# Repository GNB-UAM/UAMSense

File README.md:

# UAMSense electronic nose design
Artificial nose design with multimodal sensing capabilities.

___These are experimental designs. Use at your own risk.___

Please see Bibtex and other citation options at the bottom of the page.

UAMSense 4
==========

UAMSense 3
==========

UAMSense 2
==========

UAMSense 1
==========

UART-BME680
===========

I2C-Sensors
===========

License
=======
For source code: GPLv3 <https://www.gnu.org/licenses/gpl-3.0.en.html>

For hardware: Attribution-ShareAlike 4.0 International <https://creativecommons.org/licenses/by-sa/4.0/>

© Carlos Garcia-Saura 2023

Cite as
=======

Scientific papers:
- Garcia-Saura C., Rodriguez-Lujan I., Serrano E., Rodríguez F.B. and Varona P., At-home monitorization using artificial noses
and multimodal sensors: a noninvasive approach to human routine certification. IBJ Plus 2022 1(s5) e00017. DOI: 10.24217/2531-
0151.22v1s5.00017. https://doi.org/10.24217/2531-0151.22V1S5.00017

PhD Thesis:
```bibtex
@phdthesis{garciasaura2023,
  title={Exploration and characterization of environments under uncertainty using multimodal sensors},
  author={Garcia-Saura, Carlos},
  year={2023},
  school={Escuela Politecnica Superior, Universidad Autonoma de Madrid}
}
```

UAMSense project (this repository):
```bibtex
@misc{uamsense2023,
  author = {Garcia-Saura, Carlos},
  title = {UAMSense electronic nose design},
  publisher = {GitHub},
  year = {2023},
  doi = {10.5281/ZENODO.10442698},
  url = {https://doi.org/10.5281/zenodo.10442698}
}
```

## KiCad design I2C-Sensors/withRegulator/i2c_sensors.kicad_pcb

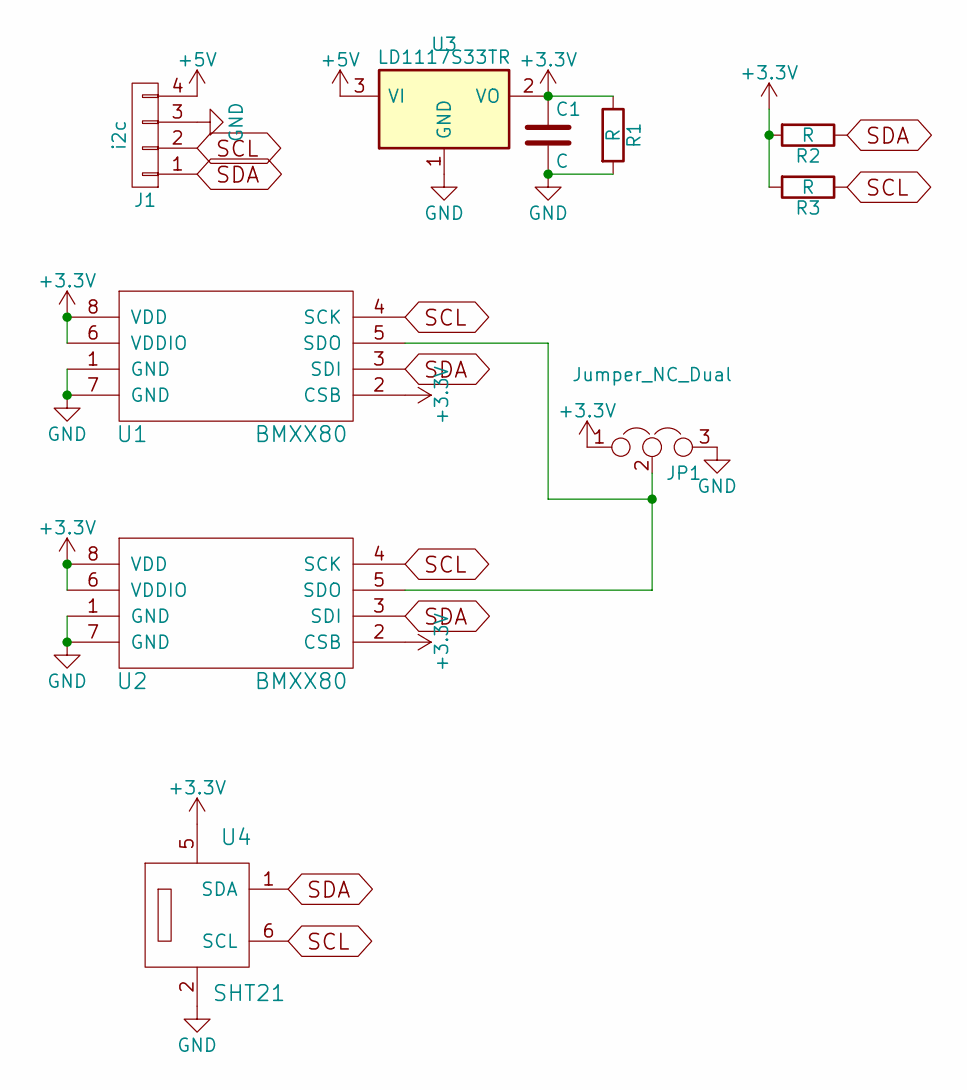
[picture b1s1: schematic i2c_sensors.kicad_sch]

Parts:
C1: C; C_0805
J1: i2c; Pin_Header_Straight_1x04_Pitch2.54mm
JP1: Jumper_NC_Dual; Pin_Header_Straight_1x03_Pitch2.54mm
R1, R2, R3: R; R_0805
U1, U2: BMXX80; BME280
U3: LD1117S33TR; SOT-223
U4: SHT21; DFN-6-1EP_3x3mm_Pitch0.95mm

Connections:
+3V3: C1.1, JP1.1, R1.1, R2.2, R3.2, U1.2 (CSB), U1.6 (VDDIO), U1.8 (VDD), U2.2 (CSB), U2.6 (VDDIO), U2.8 (VDD), U3.2 (VO), U4.5
+5V: J1.4, U3.3 (VI)
GND: C1.2, J1.3, JP1.3, R1.2, U1.1 (GND), U1.7 (GND), U2.1 (GND), U2.7 (GND), U3.1 (GND), U4.2
unnamed: JP1.2, U1.5 (SDO), U2.5 (SDO)
SCL: J1.2, R3.1, U1.4 (SCK), U2.4 (SCK), U4.6 (SCL)
SDA: J1.1, R2.1, U1.3 (SDI), U2.3 (SDI), U4.1 (SDA)

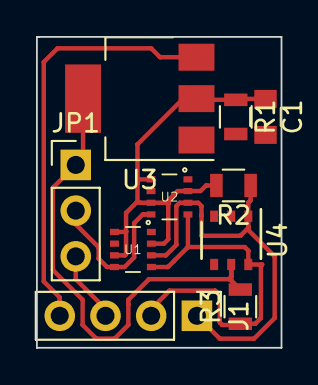
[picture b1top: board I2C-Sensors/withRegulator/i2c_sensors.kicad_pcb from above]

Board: 2 copper layers, 13.6 x 17.3 mm, 10 parts (0 on the bottom side), 6 nets.

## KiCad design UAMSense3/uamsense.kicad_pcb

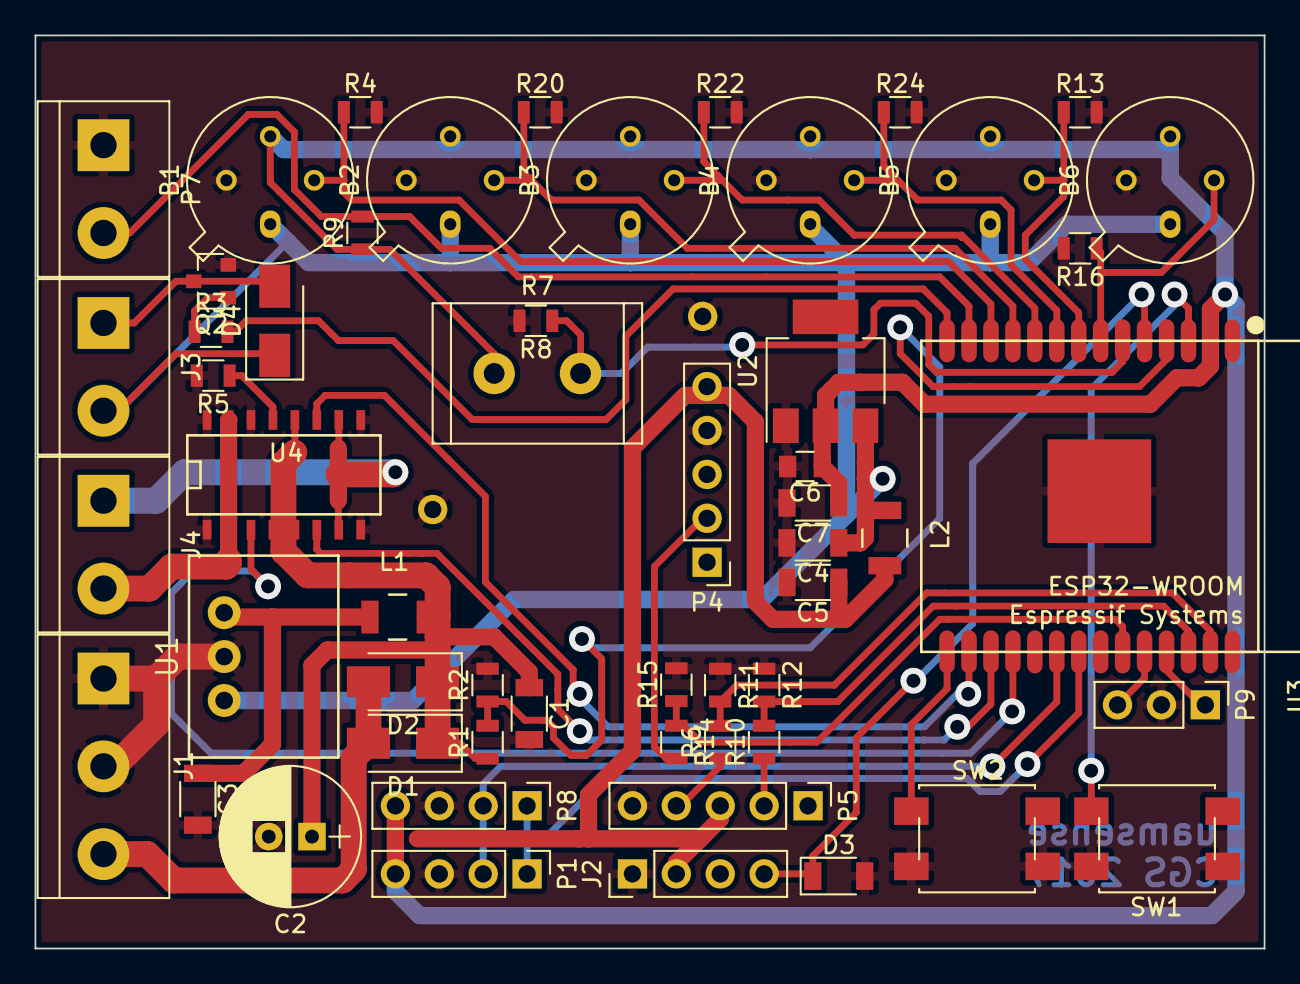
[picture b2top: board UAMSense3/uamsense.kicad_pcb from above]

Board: 2 copper layers, 71.1 x 52.8 mm, 57 parts (0 on the bottom side), 38 nets.

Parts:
B1, B2, B3, B4, B5, B6: TGS2600; TO-5-4
C1, C3, C4, C5, C7: 10u; C_1206
C2: 270u; CP_Radial_D8.0mm_P2.50mm
C6: 100n; C_0805
D1, D2, D4: D_Schottky; D_SMA
D3: 3.3V; D_1206
J1: power; bornier3
J2, J2#2, J2#3: loudness; Pin_Header_Straight_1x04_Pitch2.54mm
J3: fan; bornier2
J4: peltier; bornier2
L1, L2: 33u; Neosid_Inductor_SM-NE30_SMD1210
P1: I2C; Socket_Strip_Straight_1x04_Pitch2.54mm
P4: CDM7160; Socket_Strip_Straight_1x05_Pitch2.54mm
P5: DSM501A; Socket_Strip_Straight_1x05_Pitch2.54mm
P7: door; bornier2
P8: I2C; Pin_Header_Straight_1x04_Pitch2.54mm
P9: SERIAL; Pin_Header_Straight_1x03_Pitch2.54mm
Q2: BSS138; SOT-23
R1: R1batt; R_0805
R2: R2batt; R_0805
R3: Rfan; R_0805
R4, R13, R16, R20, R22, R24: Rtgs; R_0805
R5: RsenseH; R_0805
R6, R10: R1dust; R_0805
R7: Photores; R_Radial_Power_L12.0mm_W8.0mm_P5.00mm
R8: Rlight; R_0805
R9: Rdoor; R_0805
R11, R12: R2dust; R_0805
R14: R1co2; R_0805
R15: R2co2; R_0805
SW1: RESET; smd_button
SW2: BOOT; smd_button
U1: R-78E5.0-0.5
U2: LD1117S33TR; SOT-223
U3: ESP32-WROOM
U4: VNH7070AS; SO-16-N

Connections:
+3V3: B1.3, B2.3, B3.3, B4.3, B5.3, B6.3, C6.1, C7.1, P1.4, P8.4, R7.1, R9.1, U2.2, U3.2
+5V: C5.1, J2#3.2, L2.2, P4.5, P5.3
+5VD: B1.1, B2.1, B3.1, B4.1, B5.1, B6.1, C4.1, D4.1, J3.2, L2.1, U1.3, U2.3
+BATT: C1.1, C2.1, D1.1, D2.1, L1.2, R1.1, U4.4, U4.5, U4.12
GND: B1.4, B2.4, B3.4, B4.4, B5.4, B6.4, C1.2, C2.2, C3.2, C4.2, C5.2, C6.2, C7.2, D3.2, J1.1, J1.2, J2.1, J2#2.1, J2#3.1, P1.3, P4.4, P5.5, P7.1, P8.3, P9.2, Q2.2, R2.2, R4.2, R5.2, R8.2, R11.1, R12.1, R13.2, R15.2, R16.2, R20.2, R22.2, R24.2, SW1.1, SW2.2, U1.2, U2.1, U3.1, U3.38, U3.39, U4.1, U4.8, U4.9, U4.14, U4.16
HinA: U3.28, U4.3
HinB: U3.27, U4.6
Hpwm: U3.26, U4.11
unnamed: C3.1, L1.1, U1.1
unnamed: D1.2, D2.2, J1.3
unnamed: D4.2, J3.1, Q2.3
unnamed: J4.1, U4.7, U4.10
unnamed: J4.2, U4.2, U4.15
unnamed: P4.2, R14.2
unnamed: P5.2, R10.1
unnamed: P5.4, R6.1
unnamed: P9.1, U3.35
unnamed: P9.3, U3.34
unnamed: Q2.1, R3.1
unnamed: R5.1, U4.13
unnamed: SW1.2, U3.3
unnamed: SW2.1, U3.25
SCL: P1.2, P8.2, U3.30
SDA: P1.1, P8.1, U3.31
co2pwm: R14.1, R15.1, U3.33
dBsound: D3.1, J2#3.4, U3.5
door: P7.2, R9.2, U3.13
dust1: R6.2, R11.2, U3.37
dust2: R10.2, R12.2, U3.36
fan: R3.2, U3.14
light: R7.2, R8.1, U3.6
tgs1: B1.2, R4.1, U3.12
tgs2: B2.2, R20.1, U3.11
tgs3: B3.2, R22.1, U3.10
tgs4: B4.2, R24.1, U3.9
tgs5: B5.2, R13.1, U3.8
tgs6: B6.2, R16.1, U3.7
vBatt: R1.2, R2.1, U3.4

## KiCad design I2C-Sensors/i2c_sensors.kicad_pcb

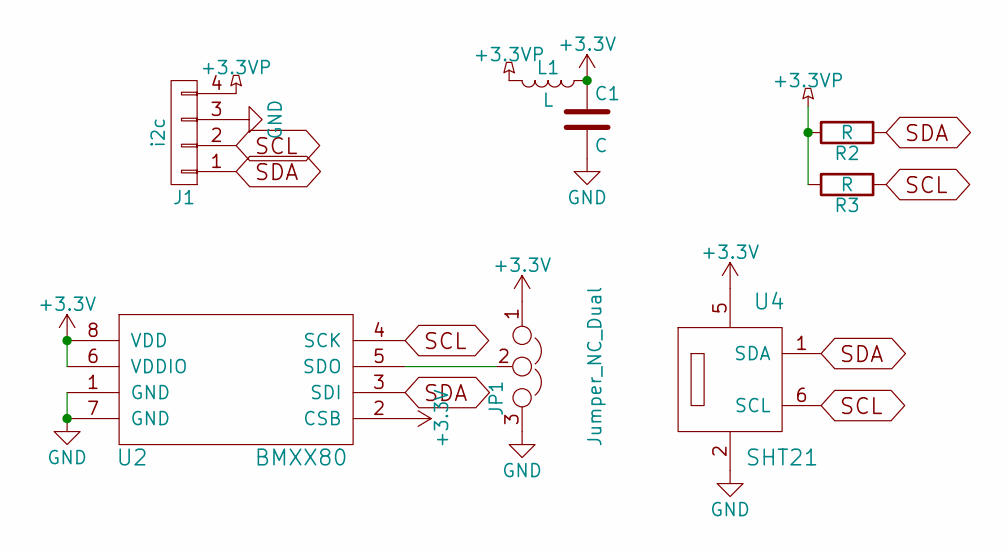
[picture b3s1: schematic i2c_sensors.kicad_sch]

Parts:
C1: C; C_0805
J1: i2c; Pin_Header_Straight_1x04_Pitch2.54mm
JP1: Jumper_NC_Dual; Pin_Header_Straight_1x03_Pitch2.54mm
L1: L; L_0805
R2, R3: R; R_0805
U2: BMXX80; BME280
U4: SHT21; DFN-6-1EP_3x3mm_Pitch0.95mm

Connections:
+3.3VP: J1.4, L1.2, R2.2, R3.2
+3V3: C1.1, JP1.1, L1.1, U2.2 (CSB), U2.6 (VDDIO), U2.8 (VDD), U4.5
GND: C1.2, J1.3, JP1.3, U2.1 (GND), U2.7 (GND), U4.2
unnamed: JP1.2, U2.5 (SDO)
SCL: J1.2, R3.1, U2.4 (SCK), U4.6 (SCL)
SDA: J1.1, R2.1, U2.3 (SDI), U4.1 (SDA)

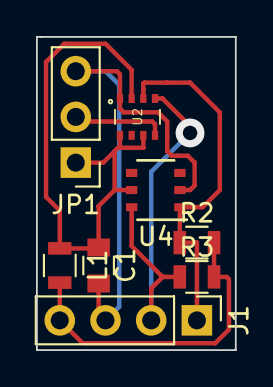
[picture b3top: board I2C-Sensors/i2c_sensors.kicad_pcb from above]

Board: 2 copper layers, 11.0 x 17.4 mm, 8 parts (0 on the bottom side), 6 nets.

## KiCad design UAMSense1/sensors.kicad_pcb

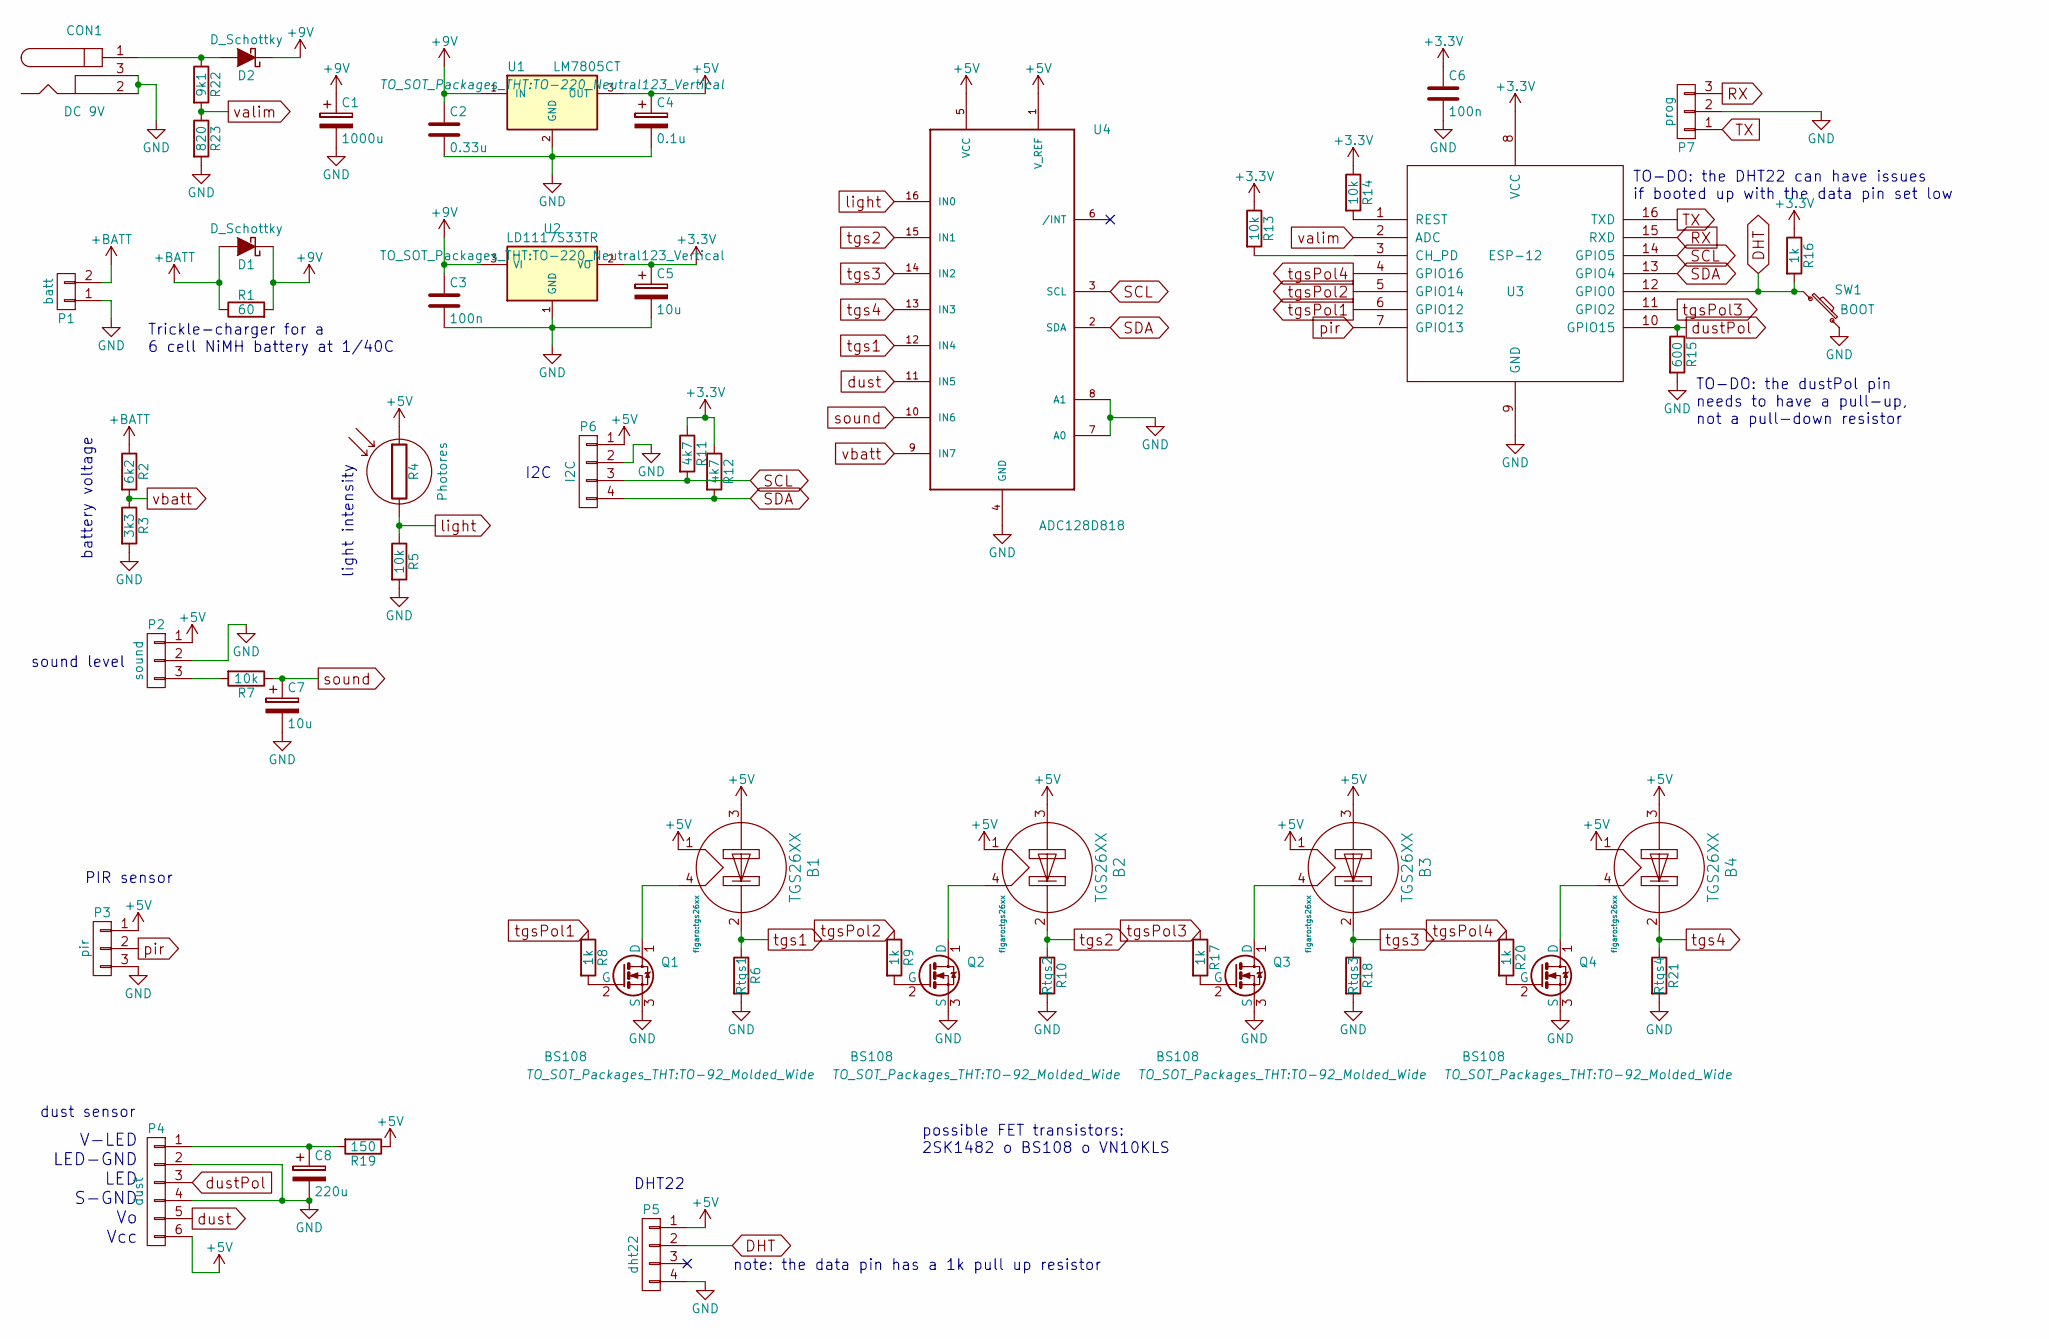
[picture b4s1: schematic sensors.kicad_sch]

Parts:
B1, B2, B3, B4: TGS26XX; tgs26xx
C1: 1000u; C_Radial_D10_L16_P5
C2: 0.33u; C_Rect_L7_W2_P5
C3: 100n; C_Rect_L7_W2_P5
C4: 0.1u; C_Radial_D8_L11.5_P3.5
C5, C7: 10u; C_Radial_D8_L11.5_P3.5
C6: 100n; C_Rect_L13_W4_P10
C8: 220u; C_Radial_D8_L11.5_P3.5
CON1: DC 9V; JACK_ALIM
D1, D2: D_Schottky; Diode_DO-41_SOD81_Vertical_KathodeUp
P1: batt; Pin_Header_Straight_1x02
P2: sound; Socket_Strip_Straight_1x03
P3: pir; Socket_Strip_Straight_1x03
P4: dust; Pin_Header_Straight_1x06
P5: dht22; Socket_Strip_Straight_1x04
P6: I2C; Socket_Strip_Straight_1x04
P7: prog; Pin_Header_Straight_1x03
Q1, Q2, Q3, Q4: BS108; TO-92_Molded_Wide
R1: 60; Resistor_Horizontal_RM20mm
R2: 6k2; Resistor_Horizontal_RM15mm
R3: 3k3; Resistor_Horizontal_RM15mm
R4: Photores; Resistor_Cement_Vertical_LargePads_KOA-BGR-5N-7N
R5, R7, R13, R14: 10k; Resistor_Horizontal_RM15mm
R6: Rtgs1; Resistor_Horizontal_RM15mm
R8, R9, R16, R17, R20: 1k; Resistor_Horizontal_RM15mm
R10: Rtgs2; Resistor_Horizontal_RM15mm
R11, R12: 4k7; Resistor_Horizontal_RM15mm
R15: 600; Resistor_Horizontal_RM15mm
R18: Rtgs3; Resistor_Horizontal_RM15mm
R19: 150; Resistor_Horizontal_RM15mm
R21: Rtgs4; Resistor_Horizontal_RM15mm
R22: 9k1; Resistor_Horizontal_RM15mm
R23: 820; Resistor_Horizontal_RM15mm
SW1: BOOT; SW_PUSH_SMALL
U1: LM7805CT; TO-220_Neutral123_Vertical
U2: LD1117S33TR; TO-220_Neutral123_Vertical
U3: ESP-12
U4: ADC128D818; SSOP-16_4.4x5.2mm_Pitch0.65mm

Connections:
+3V3: C5.1, C6.1, R11.1, R12.1, R13.1, R14.1, R16.1, U2.2 (VO), U3.8 (VCC)
+5V: B1.1, B1.3, B2.1, B2.3, B3.1, B3.3, B4.1, B4.3, C4.1, P2.1, P3.1, P4.6, P5.1, P6.1, R4.1, R19.1, U1.3 (OUT), U4.1 (V_REF), U4.5 (VCC)
+9V: C1.1, C2.1, C3.1, D1.1 (K), D2.1 (K), R1.2, U1.1 (IN), U2.3 (VI)
+BATT: D1.2 (A), P1.2, R1.1, R2.1
DHT: P5.2, R16.2, SW1.1, U3.12 (GPIO0)
GND: C1.2, C2.2, C3.2, C4.2, C5.2, C6.2, C7.2, C8.2, CON1.2, CON1.3, P1.1, P2.2, P3.3, P4.2, P4.4, P5.4, P6.2, P7.2, Q1.3 (S), Q2.3 (S), Q3.3 (S), Q4.3 (S), R3.2, R5.2, R6.2, R10.2, R15.2, R18.2, R21.2, R23.2, SW1.2, U1.2 (GND), U2.1 (GND), U3.9 (GND), U4.4 (GND), U4.7 (A0), U4.8 (A1)
unnamed: B1.4, Q1.1 (D)
unnamed: B2.4, Q2.1 (D)
unnamed: B3.4, Q3.1 (D)
unnamed: B4.4, Q4.1 (D)
unnamed: C8.1, P4.1, R19.2
unnamed: CON1.1, D2.2 (A), R22.1
unnamed: P2.3, R7.2
unnamed: Q1.2 (G), R8.2
unnamed: Q2.2 (G), R9.2
unnamed: Q3.2 (G), R17.2
unnamed: Q4.2 (G), R20.2
unnamed: R13.2, U3.3 (CH_PD)
unnamed: R14.2, U3.1 (REST)
RX: P7.3, U3.15 (RXD)
SCL: P6.3, R11.2, U3.14 (GPIO5), U4.3 (SCL)
SDA: P6.4, R12.2, U3.13 (GPIO4), U4.2 (SDA)
TX: P7.1, U3.16 (TXD)
dust: P4.5, U4.11 (IN5)
dustPol: P4.3, R15.1, U3.10 (GPIO15)
light: R4.2, R5.1, U4.16 (IN0)
pir: P3.2, U3.7 (GPIO13)
sound: C7.1, R7.1, U4.10 (IN6)
tgs1: B1.2 (-), R6.1, U4.12 (IN4)
tgs2: B2.2 (-), R10.1, U4.15 (IN1)
tgs3: B3.2 (-), R18.1, U4.14 (IN2)
tgs4: B4.2 (-), R21.1, U4.13 (IN3)
tgsPol1: R8.1, U3.6 (GPIO12)
tgsPol2: R9.1, U3.5 (GPIO14)
tgsPol3: R17.1, U3.11 (GPIO2)
tgsPol4: R20.1, U3.4 (GPIO16)
valim: R22.2, R23.1, U3.2 (ADC)
vbatt: R2.2, R3.1, U4.9 (IN7)

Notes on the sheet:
I2C
dust sensor
TO-DO: the dustPol pin needs to have a pull-up, not a pull-down resistor
Trickle-charger for a 6 cell NiMH battery at 1/40C
note: the data pin has a 1k pull up resistor
sound level
TO-DO: the DHT22 can have issues if booted up with the data pin set low
possible FET transistors: 2SK1482 o BS108 o VN10KLS
PIR sensor
DHT22
V-LED LED-GND LED S-GND Vo Vcc
battery voltage
light intensity

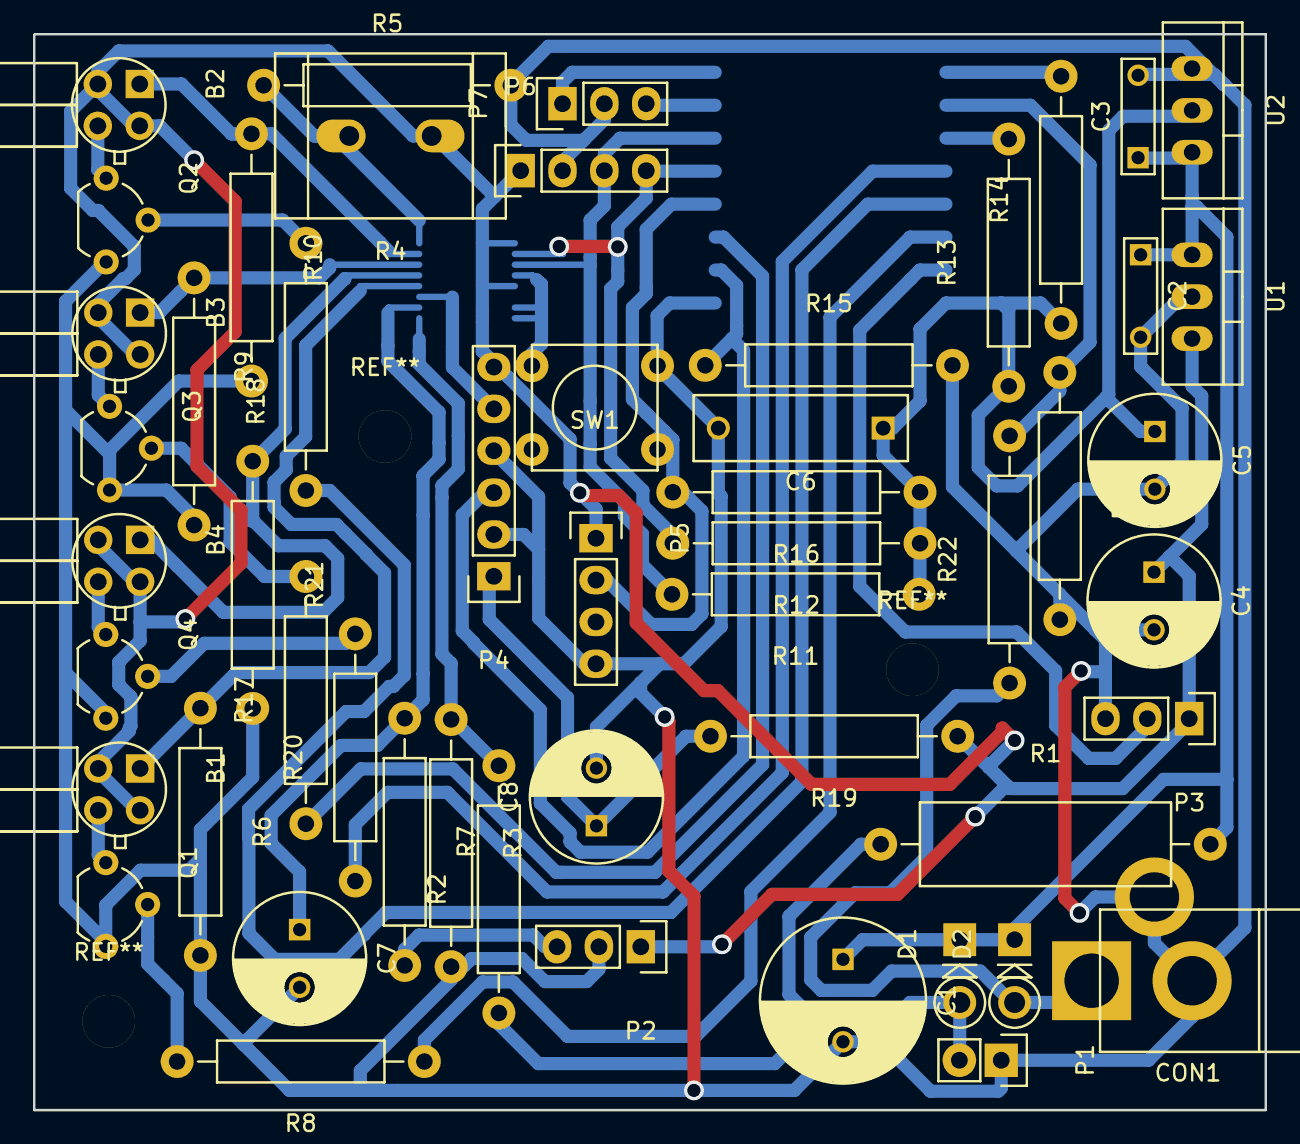
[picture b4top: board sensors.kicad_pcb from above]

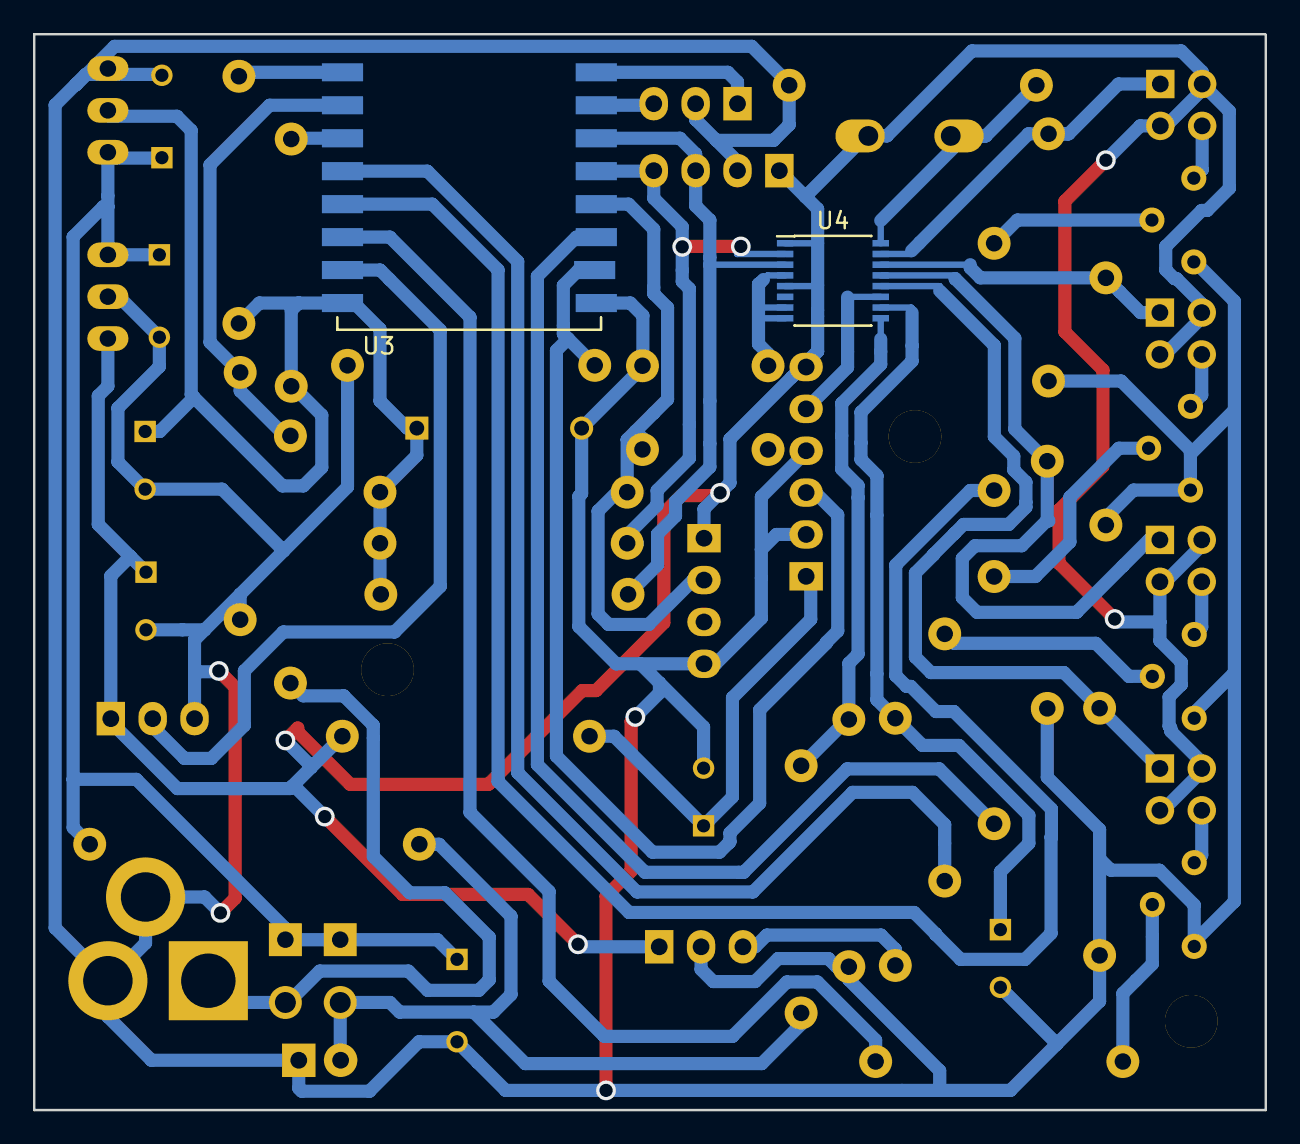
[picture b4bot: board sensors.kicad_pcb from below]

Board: 2 copper layers, 74.7 x 65.3 mm, 54 parts (2 on the bottom side), 38 nets.

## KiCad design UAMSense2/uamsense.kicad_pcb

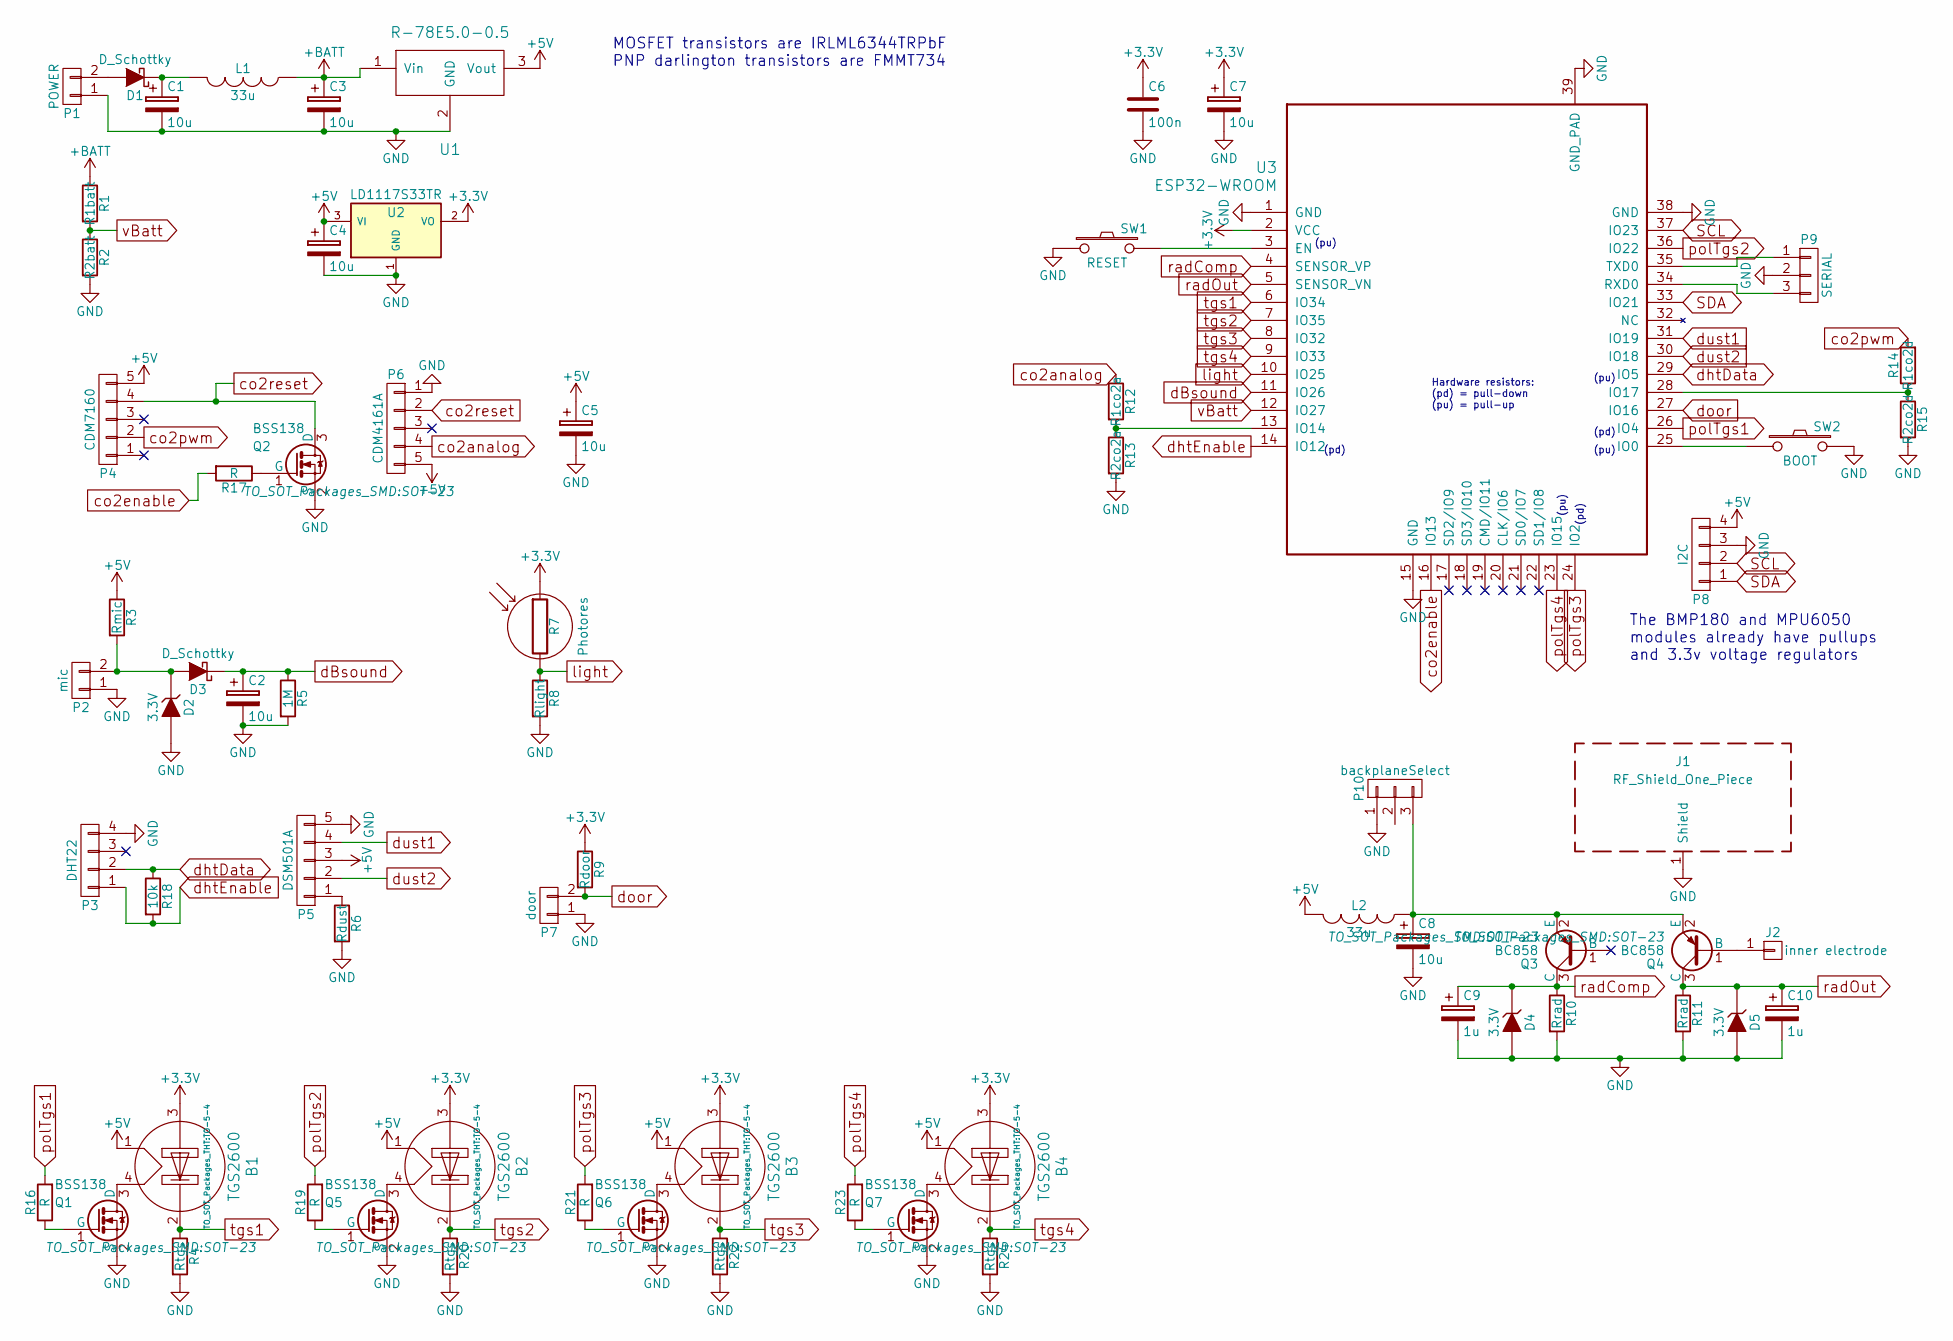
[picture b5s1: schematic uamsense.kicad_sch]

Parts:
B1, B2, B3, B4: TGS2600; TO-5-4
C1, C2, C3, C4, C5, C7, C8: 10u; C_1206
C6: 100n; C_0805
C9, C10: 1u; C_0805
D1, D3: D_Schottky; D_SMA_Standard
D2, D4, D5: 3.3V; D_1206
J1: RF_Shield_One_Piece; Laird_Technologies_BMI-S-107_44.37x44.37mm
J2: inner electrode; Measurement_Point_Round-SMD-Pad_Small
L1, L2: 33u; Neosid_Inductor_SM-NE30_SMD1210
P1: POWER; TerminalBlock_Pheonix_MPT-2.54mm_2pol
P2: mic; Socket_Strip_Straight_1x02_Pitch2.54mm
P3: DHT22; Socket_Strip_Straight_1x04_Pitch2.54mm
P4: CDM7160; Socket_Strip_Straight_1x05_Pitch2.54mm
P5: DSM501A; Socket_Strip_Straight_1x05_Pitch2.54mm
P6: CDM4161A; Socket_Strip_Angled_1x05_Pitch2.54mm
P7: door; TerminalBlock_Pheonix_MPT-2.54mm_2pol
P8: I2C; Socket_Strip_Straight_1x04_Pitch2.54mm
P9: SERIAL; Pin_Header_Straight_1x03_Pitch2.54mm
P10: backplaneSelect; Pin_Header_Straight_1x03_Pitch2.54mm
Q1, Q2, Q5, Q6, Q7: BSS138; SOT-23
Q3, Q4: BC858; SOT-23
R1: R1batt; R_0805
R2: R2batt; R_0805
R3: Rmic; R_0805
R4, R20, R22, R24: Rtgs; Resistor_SMD+THTuniversal_0805to1206_RM10_HandSoldering
R5: 1M; R_0805
R6: Rdust; R_0805
R7: Photores; R_Radial_Power_L12.0mm_W8.0mm_P5.00mm
R8: Rlight; R_0805
R9: Rdoor; R_0805
R10, R11: Rrad; R_0805
R12: R1co2a; R_0805
R13: R2co2a; R_0805
R14: R1co2d; R_0805
R15: R2co2d; R_0805
R16, R17, R19, R21, R23: R; R_0805
R18: 10k; R_0805
SW1: RESET; SW_SPST_EVQQ2
SW2: BOOT; SW_SPST_EVQQ2
U1: R-78E5.0-0.5
U2: LD1117S33TR; SOT-223
U3: ESP32-WROOM

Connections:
+3V3: B1.3, B2.3, B3.3, B4.3, C6.1, C7.1, R7.1, R9.1, U2.2 (VO), U3.2 (VCC)
+5V: B1.1, B2.1, B3.1, B4.1, C4.1, C5.1, L2.2, P4.5, P5.3, P6.5, P8.4, R3.1, U1.3 (Vout), U2.3 (VI)
+BATT: C3.1, L1.1, R1.1, U1.1 (Vin)
GND: C1.2, C2.2, C3.2, C4.2, C5.2, C6.2, C7.2, C8.2, C9.2, C10.2, D2.2 (A), D4.2 (A), D5.2 (A), J1.1, P1.1, P2.1, P3.4, P5.5, P6.1, P7.1, P8.3, P9.2, P10.1, Q1.2 (S), Q2.2 (S), Q5.2 (S), Q6.2 (S), Q7.2 (S), R2.2, R4.2, R5.2, R6.2, R8.2, R10.2, R11.2, R13.2, R15.2, R20.2, R22.2, R24.2, SW1.1, SW2.2, U1.2 (GND), U2.1 (GND), U3.1 (GND), U3.15 (GND), U3.38 (GND), U3.39 (GND_PAD)
unnamed: B1.4, Q1.3 (D)
unnamed: B2.4, Q5.3 (D)
unnamed: B3.4, Q6.3 (D)
unnamed: B4.4, Q7.3 (D)
unnamed: C1.1, D1.1 (K), L1.2
unnamed: C8.1, L2.1, P10.3, Q3.2 (E), Q4.2 (E)
unnamed: D1.2 (A), P1.2
unnamed: D2.1 (K), D3.2 (A), P2.2, R3.2
unnamed: J2.1, Q4.1 (B)
unnamed: P5.1, R6.1
unnamed: P9.1, U3.35 (TXD0)
unnamed: P9.3, U3.34 (RXD0)
unnamed: Q1.1 (G), R16.1
unnamed: Q2.1 (G), R17.1
unnamed: Q5.1 (G), R19.1
unnamed: Q6.1 (G), R21.1
unnamed: Q7.1 (G), R23.1
unnamed: R12.2, R13.1, U3.13 (IO14)
unnamed: R14.1, R15.1, U3.28 (IO17)
unnamed: SW1.2, U3.3 (EN)
unnamed: SW2.1, U3.25 (IO0)
SCL: P8.2, U3.37 (IO23)
SDA: P8.1, U3.33 (IO21)
co2analog: P6.4, R12.1
co2enable: R17.2, U3.16 (IO13)
co2pwm: P4.2, R14.2
co2reset: P4.4, P6.2, Q2.3 (D)
dBsound: C2.1, D3.1 (K), R5.1, U3.11 (IO26)
dhtData: P3.2, R18.1, U3.29 (IO5)
dhtEnable: P3.1, R18.2, U3.14 (IO12)
door: P7.2, R9.2, U3.27 (IO16)
dust1: P5.4, U3.31 (IO19)
dust2: P5.2, U3.30 (IO18)
light: R7.2, R8.1, U3.10 (IO25)
polTgs1: R16.2, U3.26 (IO4)
polTgs2: R19.2, U3.36 (IO22)
polTgs3: R21.2, U3.24 (IO2)
polTgs4: R23.2, U3.23 (IO15)
radComp: C9.1, D4.1 (K), Q3.3 (C), R10.1, U3.4 (SENSOR_VP)
radOut: C10.1, D5.1 (K), Q4.3 (C), R11.1, U3.5 (SENSOR_VN)
tgs1: B1.2 (-), R4.1, U3.6 (IO34)
tgs2: B2.2 (-), R20.1, U3.7 (IO35)
tgs3: B3.2 (-), R22.1, U3.8 (IO32)
tgs4: B4.2 (-), R24.1, U3.9 (IO33)
vBatt: R1.2, R2.1, U3.12 (IO27)

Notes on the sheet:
Hardware resistors: (pd) = pull-down (pu) = pull-up
(pu)
The BMP180 and MPU6050 modules already have pullups and 3.3v voltage regulators
(pd)
MOSFET transistors are IRLML6344TRPbF PNP darlington transistors are FMMT734

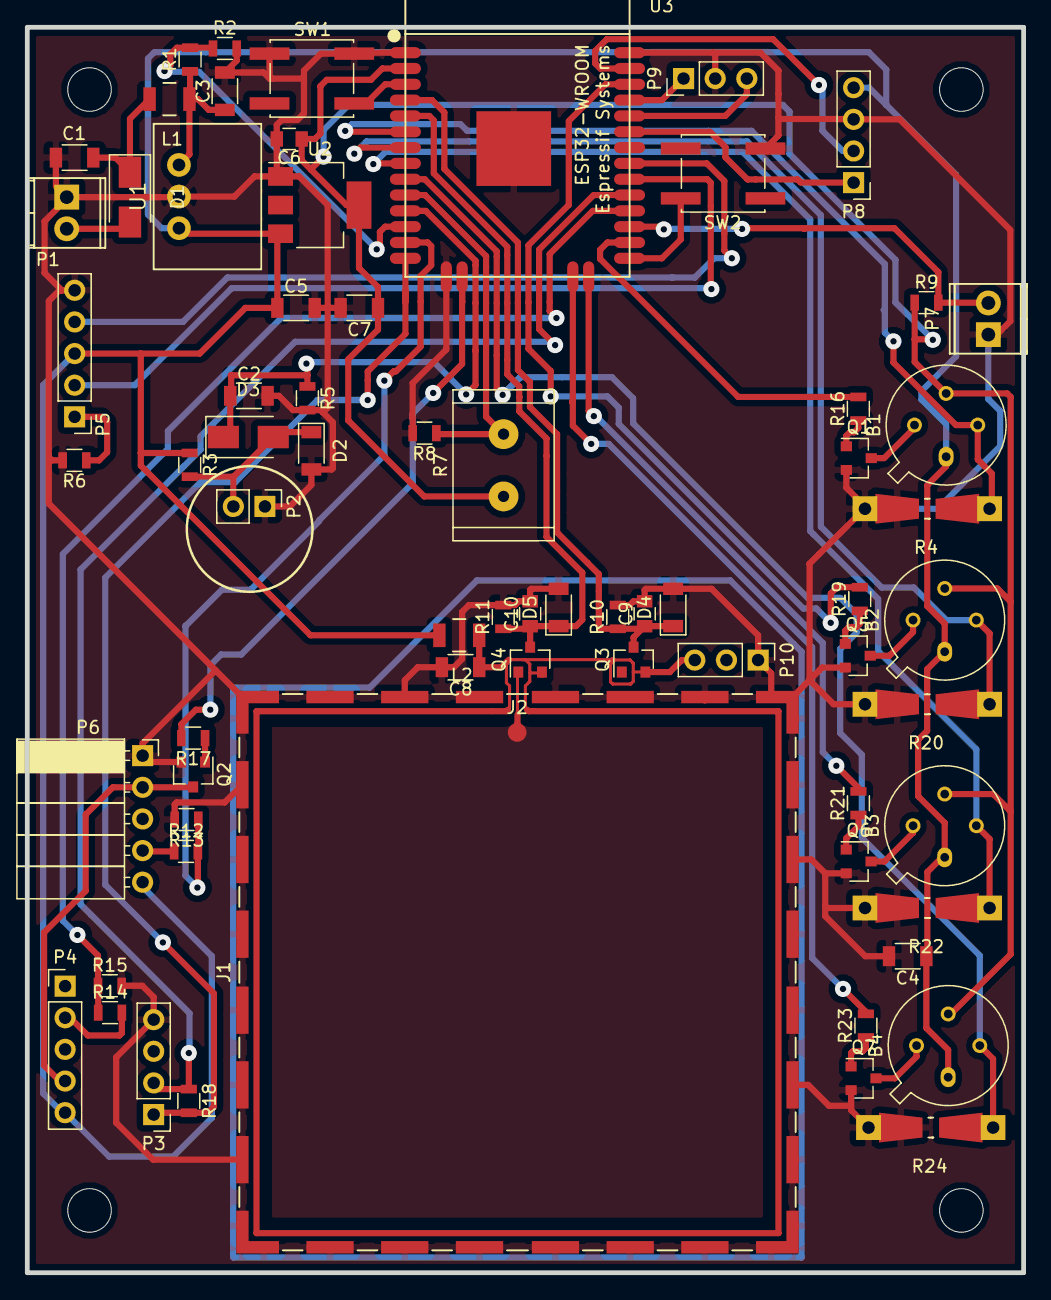
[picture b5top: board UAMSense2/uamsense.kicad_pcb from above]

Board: 2 copper layers, 80.0 x 100.0 mm, 69 parts (0 on the bottom side), 49 nets.

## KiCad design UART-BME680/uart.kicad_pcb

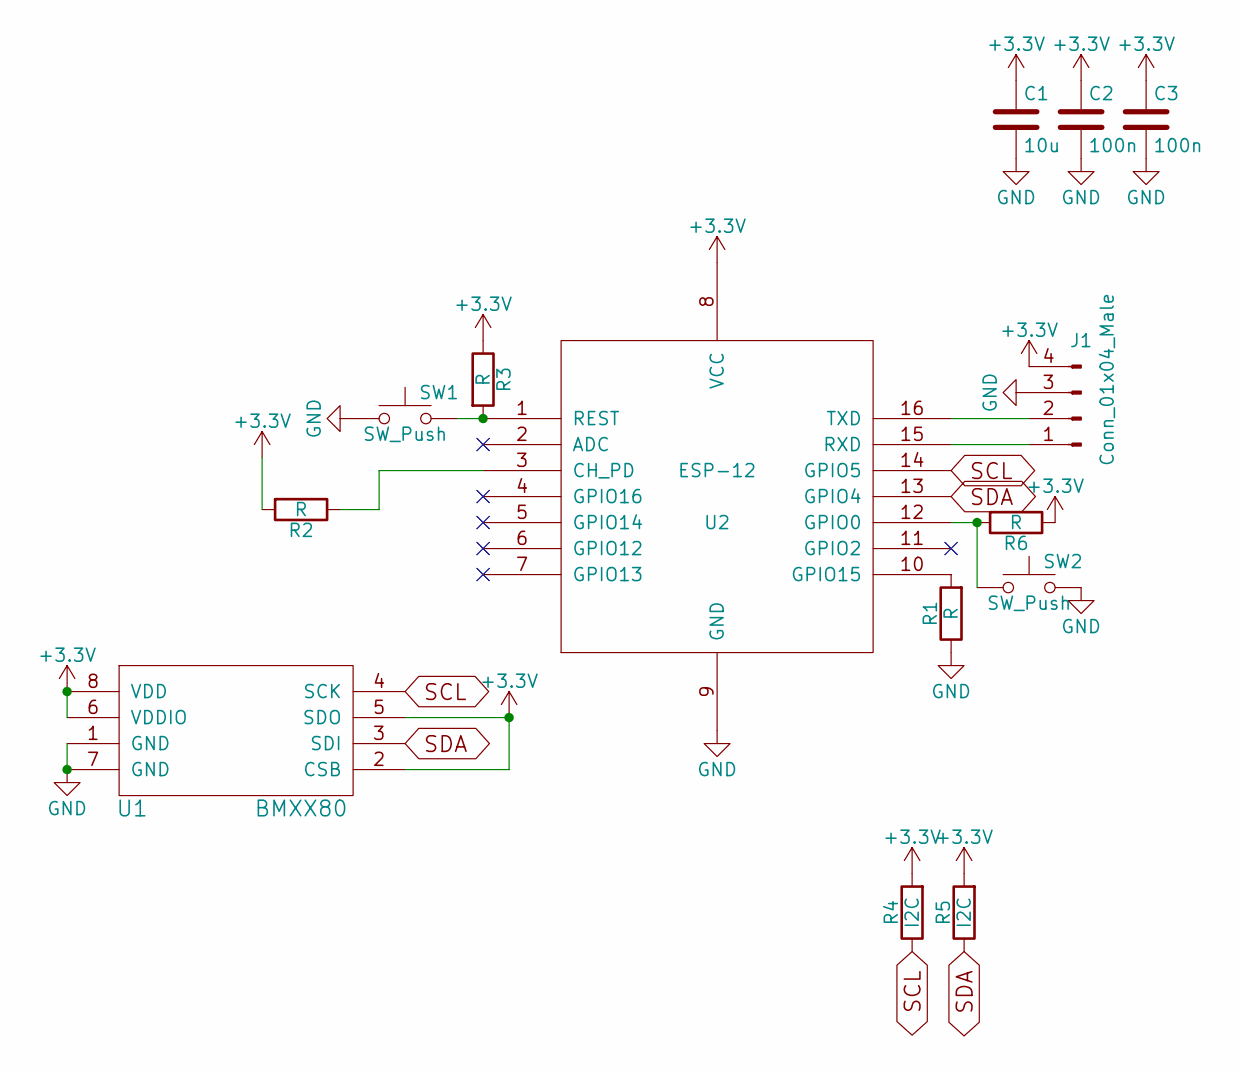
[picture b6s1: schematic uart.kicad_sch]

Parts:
C1: 10u; C_1206_HandSoldering
C2, C3: 100n; C_0805_HandSoldering
J1: Conn_01x04_Male; Pin_Header_Angled_1x04_Pitch2.54mm
R1, R2, R3, R6: R; R_0805_HandSoldering
R4, R5: I2C; R_0805_HandSoldering
SW1, SW2: SW_Push; smd_button
U1: BMXX80; BME280
U2: ESP-12

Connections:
+3V3: C1.1, C2.1, C3.1, J1.4, R2.2, R3.1, R4.2, R5.2, R6.1, U1.2 (CSB), U1.5 (SDO), U1.6 (VDDIO), U1.8 (VDD), U2.8 (VCC)
GND: C1.2, C2.2, C3.2, J1.3, R1.1, SW1.1, SW2.2, U1.1 (GND), U1.7 (GND), U2.9 (GND)
unnamed: J1.1, U2.15 (RXD)
unnamed: J1.2, U2.16 (TXD)
unnamed: R1.2, U2.10 (GPIO15)
unnamed: R2.1, U2.3 (CH_PD)
unnamed: R3.2, SW1.2, U2.1 (REST)
unnamed: R6.2, SW2.1, U2.12 (GPIO0)
SCL: R4.1, U1.4 (SCK), U2.14 (GPIO5)
SDA: R5.1, U1.3 (SDI), U2.13 (GPIO4)

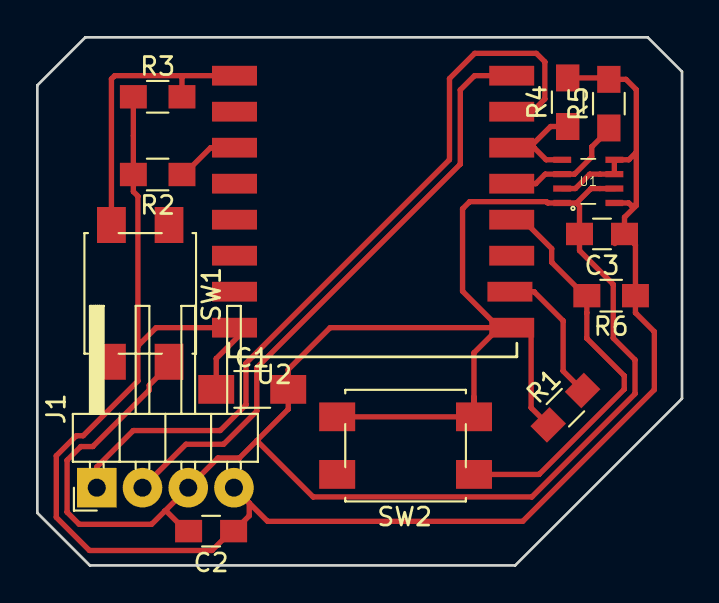
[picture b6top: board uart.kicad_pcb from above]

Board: 2 copper layers, 35.8 x 29.3 mm, 14 parts (0 on the bottom side), 10 nets.

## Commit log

2023-12-31 Included DOI and Bibtex citation references
